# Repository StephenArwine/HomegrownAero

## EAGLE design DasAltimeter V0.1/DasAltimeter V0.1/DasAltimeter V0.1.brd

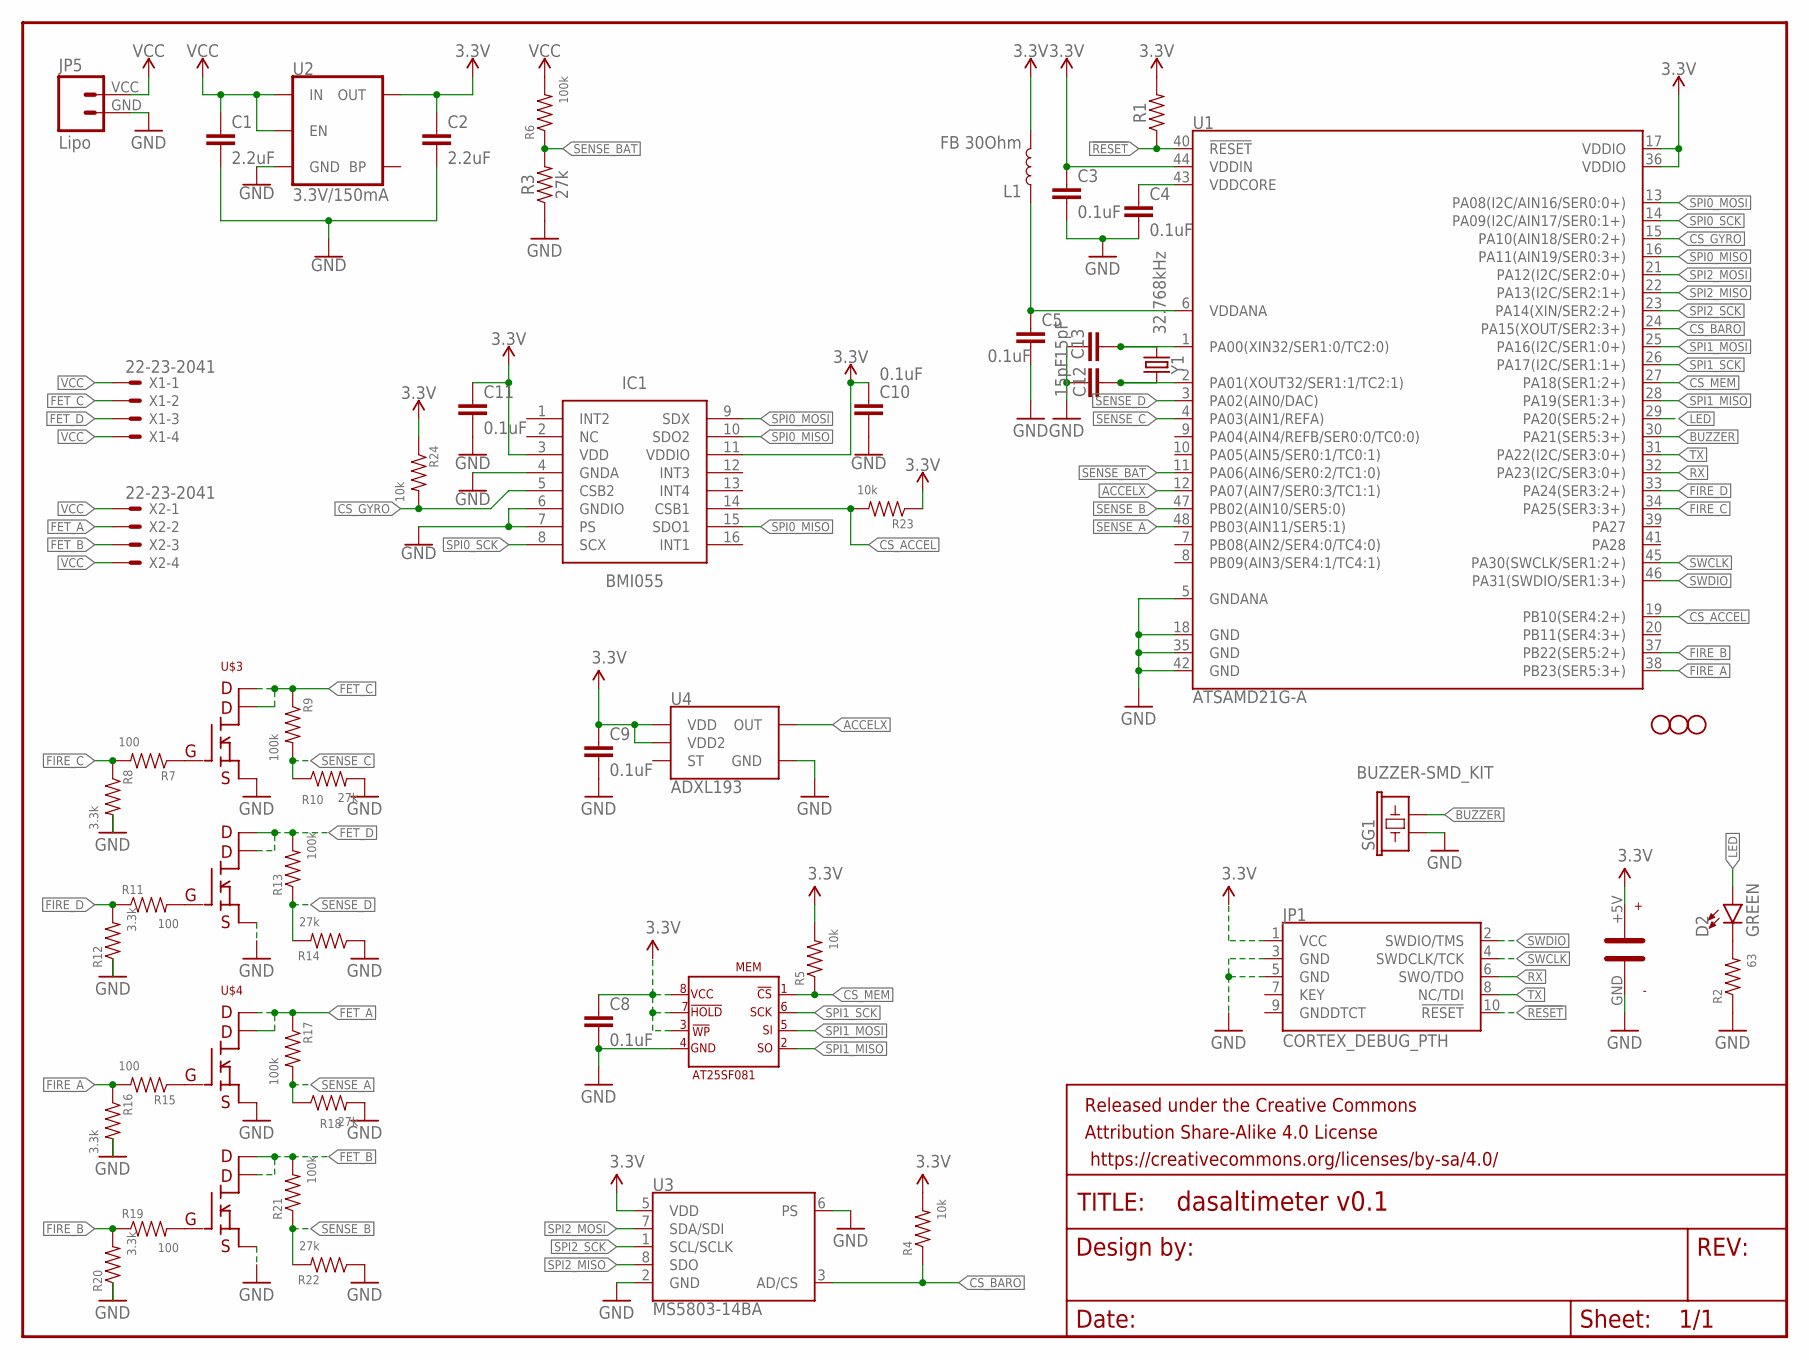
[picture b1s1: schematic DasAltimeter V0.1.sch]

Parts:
C1, C2: 2.2uF; 0603
C3, C4, C5, C8, C9, C10, C11: 0.1uF; 0402
C12, C13: 15pF; 0402
D2: GREEN; LED-1206
FRAME1: FRAME-LETTERNO_PACKAGE; DUMMY
H1, H2, H3: STAND-OFFTIGHT; STAND-OFF-TIGHT
IC1: BMI055
JP1: CORTEX_DEBUG_PTH; 2X5-PTH-1.27MM
JP5: Lipo; JST-2-SMD-VERT
L1: FB 30Ohm; 0603
MEM: AT25SF081
R1: 0402
R2: 63; 0402
R3, R10, R14, R18, R22: 27k; 0402
R4, R5, R23, R24: 10k; 0402
R6, R9, R13, R17, R21: 100k; 0402
R7, R11, R15, R19: 100; 0402
R8, R12, R16, R20: 3.3k; 0402
SG1: BUZZER-SMD_KIT; BUZZER-CCV-KIT
U1: ATSAMD21G-A; TQFP-48
U2: 3.3V/150mA; SOT23-5
U3: MS5803-14BA; MS5803
U4: ADXL193; LCC-8
U$1: PB-5R0H104-R
U$3, U$4: SI7232DN
X1, X2: 22-23-2041
Y1: 32.768kHz; CRYSTAL-SMD-3.2X1.5MM

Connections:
3.3V: C2.1, C3.1, C8.1, C9.1, C10.1, C11.1, IC1.3 (VDD), IC1.11 (VDDIO), JP1.1 (VCC), L1.2, MEM.!HOLD, MEM.!WP, MEM.VCC, R1.2, R4.2, R5.2, R23.1, R24.1, U1.17 (VDDIO), U1.36 (VDDIO), U1.44 (VDDIN), U2.5 (OUT), U3.5 (VDD), U4.P$7 (VDD), U4.P$8 (VDD2), U$1.+5V
!RESET: JP1.10 (!RESET), R1.1, U1.40 (!RESET!)
ACCELX: U1.12 (PA07(AIN7/SER0:3/TC1:1)), U4.P$6 (OUT)
BUZZER: SG1.- (2), U1.30 (PA21(SER5:3+))
CS_ACCEL: IC1.14 (CSB1), R23.2, U1.19 (PB10(SER4:2+))
CS_GYRO: IC1.5 (CSB2), R24.2, U1.15 (PA10(AIN18/SER0:2+))
CS_MEM: MEM.!CS, R5.1, U1.27 (PA18(SER1:2+))
FET_A: R17.1, U$4.7 (PIN7), U$4.8 (PIN8), U$4.9 (PIN8), X2.2
FET_B: R21.2, U$4.5 (PIN5), U$4.6 (PIN6), U$4.10 (PIN5), X2.3
FET_C: R9.1, U$3.7 (PIN7), U$3.8 (PIN8), U$3.9 (PIN8), X1.2
FET_D: R13.2, U$3.5 (PIN5), U$3.6 (PIN6), U$3.10 (PIN5), X1.3
FIRE_A: R15.2, R16.1, U1.38 (PB23(SER5:3+))
FIRE_B: R19.1, R20.2, U1.37 (PB22(SER5:2+))
FIRE_C: R7.2, R8.1, U1.34 (PA25(SER3:3+))
FIRE_D: R11.1, R12.2, U1.33 (PA24(SER3:2+))
GND: C1.2, C2.2, C3.2, C4.2, C5.2, C8.2, C9.2, C10.2, C11.2, C12.1, C13.1, IC1.4 (GNDA), IC1.6 (GNDIO), IC1.7 (PS), JP1.3 (GND), JP1.5 (GND), JP5.GND (1), MEM.GND, R2.1, R3.1, R8.2, R10.2, R12.1, R14.1, R16.2, R18.2, R20.1, R22.1, SG1.+ (1), U1.5 (GNDANA), U1.18 (GND), U1.35 (GND), U1.42 (GND), U2.2 (GND), U3.2 (GND), U3.6 (PS), U4.P$3 (GND), U$1.GND, U$3.1 (PIN1), U$3.3 (PIN3), U$4.1 (PIN1), U$4.3 (PIN3)
LED: D2.A, U1.29 (PA20(SER5:2+))
unnamed: R7.1, U$3.2 (PIN2)
unnamed: C4.1, U1.43 (VDDCORE)
unnamed: C5.1, L1.1, U1.6 (VDDANA)
unnamed: C13.2, U1.1 (PA00(XIN32/SER1:0/TC2:0)), Y1.P$2 (2)
unnamed: C12.2, U1.2 (PA01(XOUT32/SER1:1/TC2:1)), Y1.P$1 (1)
unnamed: R11.2, U$3.4 (PIN4)
unnamed: R15.1, U$4.2 (PIN2)
unnamed: R19.2, U$4.4 (PIN4)
unnamed: D2.C, R2.2
RX: JP1.6 (SWO/TDO), U1.32 (PA23(I2C/SER3:0+))
SENSE_A: R17.2, R18.1, U1.48 (PB03(AIN11/SER5:1))
SENSE_B: R21.1, R22.2, U1.47 (PB02(AIN10/SER5:0))
SENSE_BAT: R3.2, R6.1, U1.11 (PA06(AIN6/SER0:2/TC1:0))
SENSE_C: R9.2, R10.1, U1.4 (PA03(AIN1/REFA))
SENSE_D: R13.1, R14.2, U1.3 (PA02(AIN0/DAC))
SPI0_MISO: IC1.10 (SDO2), IC1.15 (SDO1), U1.16 (PA11(AIN19/SER0:3+))
SPI0_MOSI: IC1.9 (SDX), U1.13 (PA08(I2C/AIN16/SER0:0+))
SPI0_SCK: IC1.8 (SCX), U1.14 (PA09(I2C/AIN17/SER0:1+))
SPI1_MISO: MEM.SO, U1.28 (PA19(SER1:3+))
SPI1_MOSI: MEM.SI, U1.25 (PA16(I2C/SER1:0+))
SPI1_SCK: MEM.SCK, U1.26 (PA17(I2C/SER1:1+))
SPI2_MISO: U1.22 (PA13(I2C/SER2:1+)), U3.8 (SDO)
SPI2_MOSI: U1.21 (PA12(I2C/SER2:0+)), U3.7 (SDA/SDI)
SWCLK: JP1.4 (SWDCLK/TCK), U1.45 (PA30(SWCLK/SER1:2+))
SWDIO: JP1.2 (SWDIO/TMS), U1.46 (PA31(SWDIO/SER1:3+))
TX: JP1.8 (NC/TDI), U1.31 (PA22(I2C/SER3:0+))
VCC: C1.1, JP5.VCC (2), R6.2, U2.1 (IN), U2.3 (EN), X1.1, X1.4, X2.1, X2.4

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
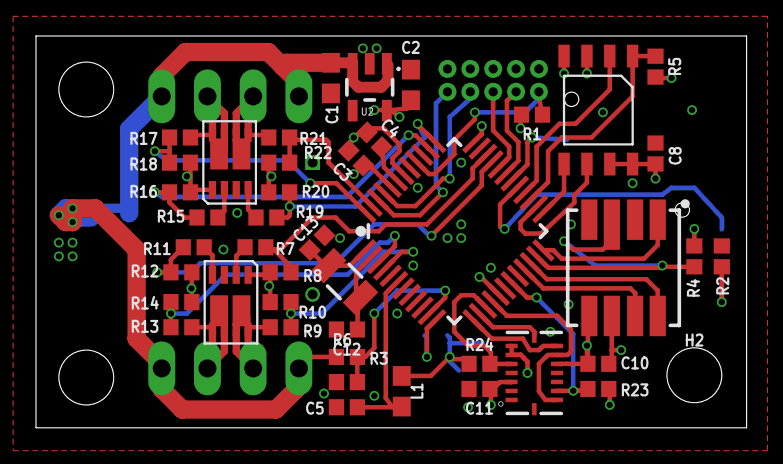
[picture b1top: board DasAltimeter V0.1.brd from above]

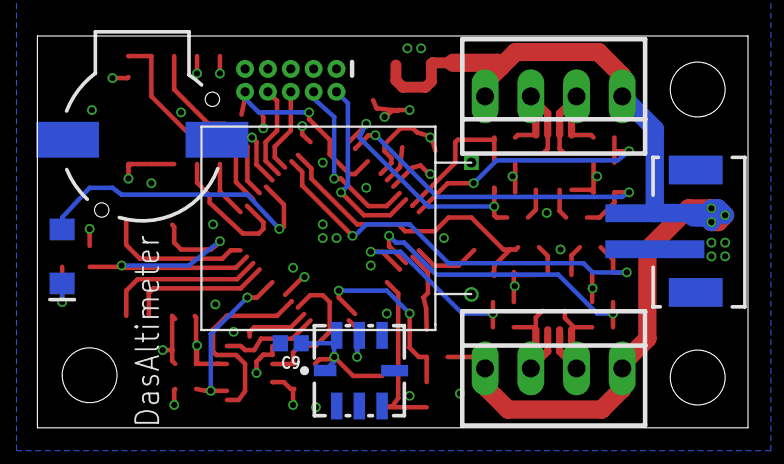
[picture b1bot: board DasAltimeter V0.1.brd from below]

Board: 4 copper layers, 39.5 x 21.8 mm, 56 parts (9 on the bottom side), 46 nets.

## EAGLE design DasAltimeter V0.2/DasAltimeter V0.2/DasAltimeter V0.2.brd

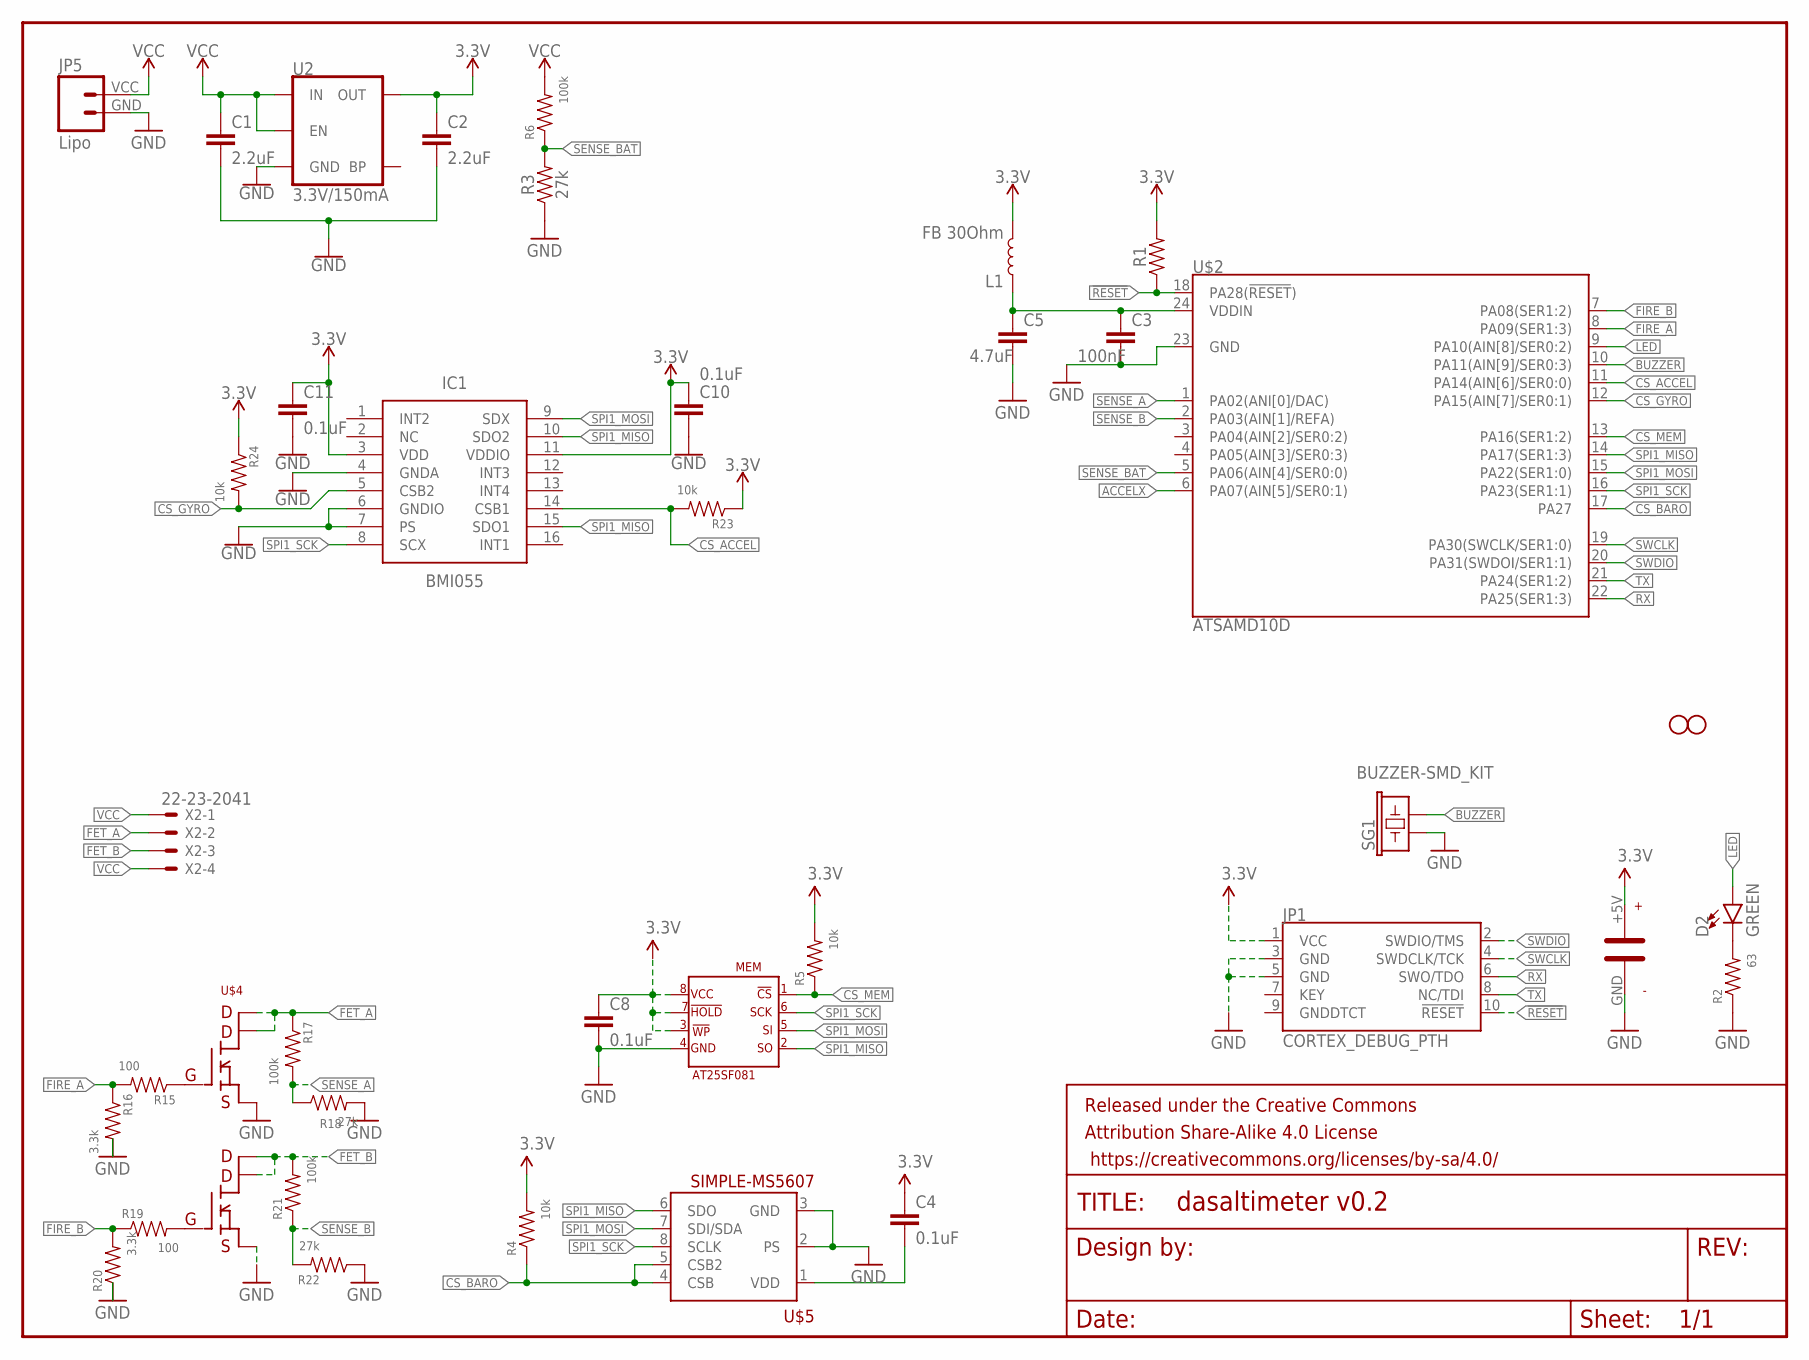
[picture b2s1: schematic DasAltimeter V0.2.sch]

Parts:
C1, C2: 2.2uF; 0603
C3: 100nF; 0402
C4, C8, C10, C11: 0.1uF; 0402
C5: 4.7uF; 0402
D2: GREEN; LED-1206
FRAME1: FRAME-LETTERNO_PACKAGE; DUMMY
H2, H3: STAND-OFFTIGHT; STAND-OFF-TIGHT
IC1: BMI055
JP1: CORTEX_DEBUG_PTH; 2X5-PTH-1.27MM
JP5: Lipo; JST-2-SMD-VERT
L1: FB 30Ohm; 0603
MEM: AT25SF081
R1: 0402
R2: 63; 0402
R3, R18, R22: 27k; 0402
R4, R5, R23, R24: 10k; 0402
R6, R17, R21: 100k; 0402
R15, R19: 100; 0402
R16, R20: 3.3k; 0402
SG1: BUZZER-SMD_KIT; BUZZER-CCV-KIT
U2: 3.3V/150mA; SOT23-5
U$1: PB-5R0H104-R
U$2: ATSAMD10D
U$4: SI7232DN
U$5: SIMPLE-MS5607; MS5607
X2: 22-23-2041

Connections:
3.3V: C2.1, C4.1, C8.1, C10.1, C11.1, IC1.3 (VDD), IC1.11 (VDDIO), JP1.1 (VCC), L1.2, MEM.!HOLD, MEM.!WP, MEM.VCC, R1.2, R4.2, R5.2, R23.1, R24.1, U2.5 (OUT), U$1.+5V
!RESET: JP1.10 (!RESET), R1.1, U$2.18 (PA28(!RESET!))
ACCELX: U$2.6 (PA07(AIN[5]/SER0:1))
BUZZER: SG1.- (2), U$2.10 (PA11(AIN[9]/SER0:3))
CS_ACCEL: IC1.14 (CSB1), R23.2, U$2.11 (PA14(AIN[6]/SER0:0))
CS_BARO: R4.1, U$2.17 (PA27), U$5.5 (CSB2)
CS_GYRO: IC1.5 (CSB2), R24.2, U$2.12 (PA15(AIN[7]/SER0:1))
CS_MEM: MEM.!CS, R5.1, U$2.13 (PA16(SER1:2))
FET_A: R17.1, U$4.7 (PIN7), U$4.8 (PIN8), U$4.9 (PIN8), X2.2
FET_B: R21.2, U$4.5 (PIN5), U$4.6 (PIN6), U$4.10 (PIN5), X2.3
FIRE_A: R15.2, R16.1, U$2.8 (PA09(SER1:3))
FIRE_B: R19.1, R20.2, U$2.7 (PA08(SER1:2))
GND: C1.2, C2.2, C3.2, C5.2, C8.2, C10.2, C11.2, IC1.4 (GNDA), IC1.6 (GNDIO), IC1.7 (PS), JP1.3 (GND), JP1.5 (GND), JP5.GND (1), MEM.GND, R2.1, R3.1, R16.2, R18.2, R20.1, R22.1, SG1.+ (1), U2.2 (GND), U$1.GND, U$2.23 (GND), U$4.1 (PIN1), U$4.3 (PIN3), U$5.3 (GND)
LED: D2.A, U$2.9 (PA10(AIN[8]/SER0:2))
unnamed: C4.2, U$5.1 (VDD)
unnamed: C3.1, C5.1, L1.1, U$2.24 (VDDIN)
unnamed: R15.1, U$4.2 (PIN2)
unnamed: R19.2, U$4.4 (PIN4)
unnamed: D2.C, R2.2
RX: JP1.6 (SWO/TDO), U$2.22 (PA25(SER1:3))
SENSE_A: R17.2, R18.1, U$2.1 (PA02(ANI[0]/DAC))
SENSE_B: R21.1, R22.2, U$2.2 (PA03(AIN[1]/REFA))
SENSE_BAT: R3.2, R6.1, U$2.5 (PA06(AIN[4]/SER0:0))
SPI1_MISO: IC1.10 (SDO2), IC1.15 (SDO1), MEM.SO, U$2.14 (PA17(SER1:3))
SPI1_MOSI: IC1.9 (SDX), MEM.SI, U$2.15 (PA22(SER1:0))
SPI1_SCK: IC1.8 (SCX), MEM.SCK, U$2.16 (PA23(SER1:1))
SWCLK: JP1.4 (SWDCLK/TCK), U$2.19 (PA30(SWCLK/SER1:0))
SWDIO: JP1.2 (SWDIO/TMS), U$2.20 (PA31(SWDOI/SER1:1))
TX: JP1.8 (NC/TDI), U$2.21 (PA24(SER1:2))
VCC: C1.1, JP5.VCC (2), R6.2, U2.1 (IN), U2.3 (EN), X2.1, X2.4

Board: 4 copper layers, 40 parts (9 on the bottom side), 29 nets, no tracks yet.

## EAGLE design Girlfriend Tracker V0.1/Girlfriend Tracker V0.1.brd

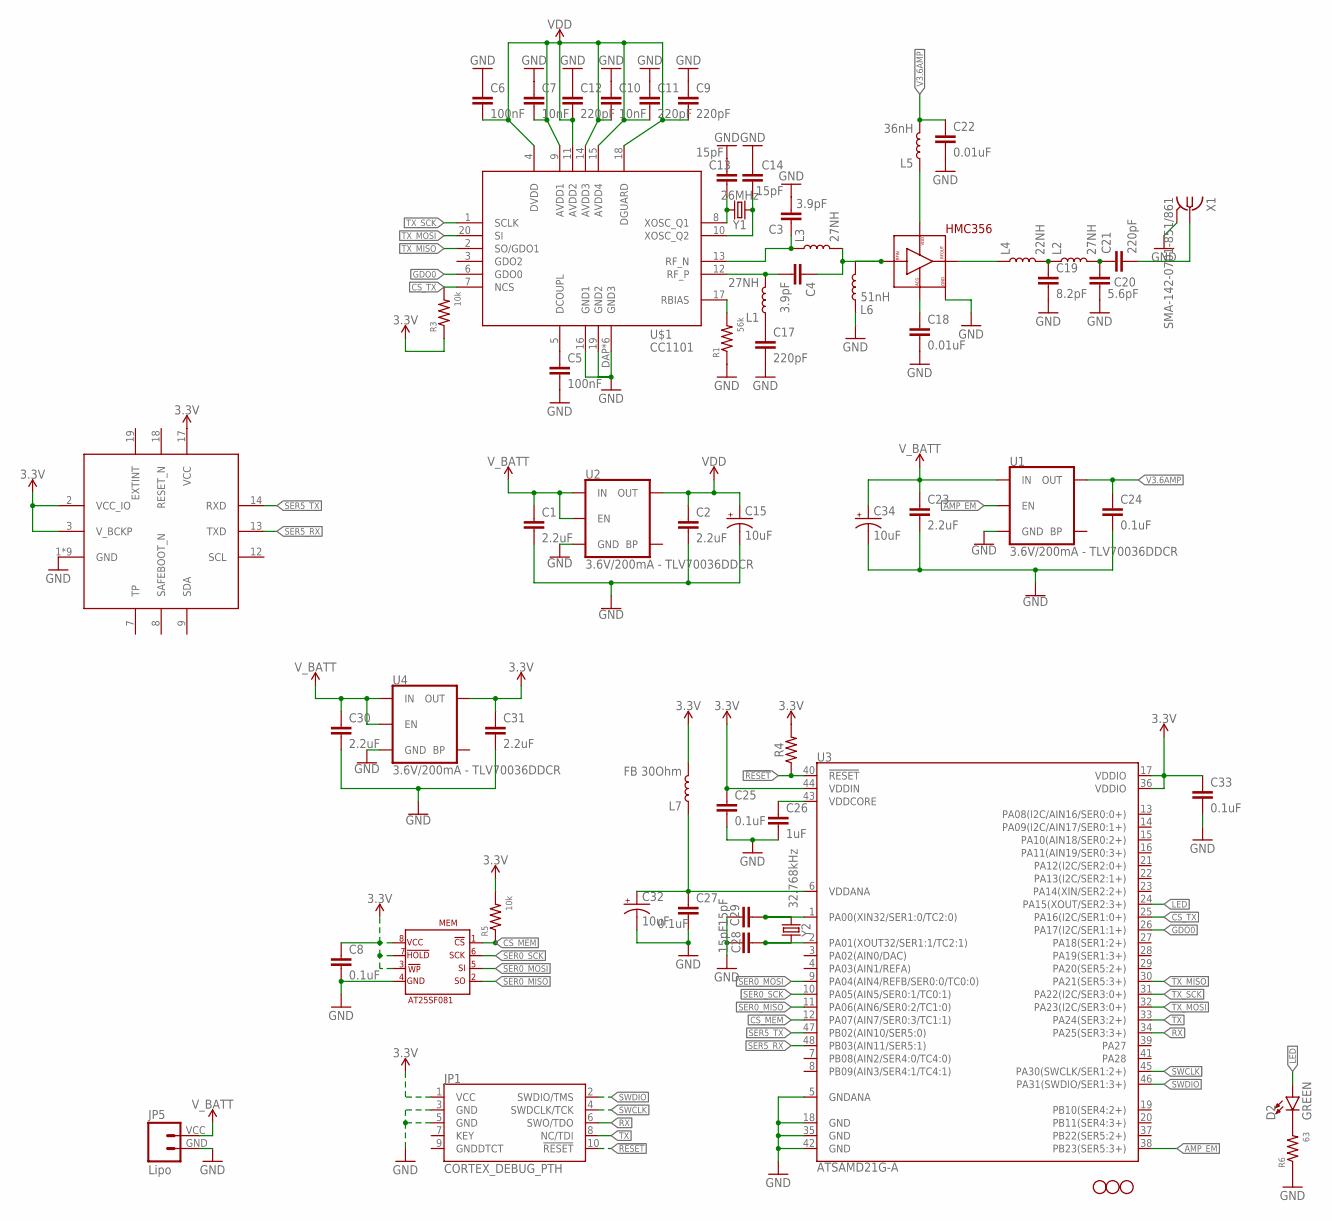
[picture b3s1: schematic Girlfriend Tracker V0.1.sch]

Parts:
C1, C2, C23, C30, C31: 2.2uF; 0603
C3, C4: 3.9pF; 0402
C5, C6: 100nF; 0402
C7, C10: 10nF; 0402
C8, C25, C27, C33: 0.1uF; 0402
C9, C11, C12, C17, C21: 220pF; 0402
C13, C14, C28, C29: 15pF; 0402
C15, C32, C34: 10uF; EIA3216
C18, C22: 0.01uF; 0402
C19: 8.2pF; 0402
C20: 5.6pF; 0402
C24: 0.1uF; 0603
C26: 1uF; 0402
D2: GREEN; LED-1206
H1, H2, H3: STAND-OFFTIGHT; STAND-OFF-TIGHT
IC1: SAM-M8Q
JP1: CORTEX_DEBUG_PTH; 2X5-PTH-1.27MM
JP5: Lipo; JST-2-SMD-VERT
L1, L2, L3: 27NH; 0402
L4: 22NH; 0402
L5: 36nH; 0402
L6: 51nH; 0402
L7: FB 30Ohm; 0603
MEM: AT25SF081
R1: 56k; 0402
R3, R5: 10k; 0402
R4: 0402
R6: 63; 0402
U1, U2, U4: 3.6V/200mA - TLV70036DDCR; SOT23-5
U3: ATSAMD21G-A; TQFP-48
U$1: CC1101
U$3: HMC356; QFN16_HMC356
X1: SMA-142-0701-851/861; J502-ND-142-0701-851/861
Y1: 26MHz; CRYSTAL-SMD-3.2X2.5MM
Y2: 32.768kHz; CRYSTAL-SMD-3.2X1.5MM

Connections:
3.3V: C8.1, C25.1, C31.1, C33.1, IC1.2 (VCC_IO), IC1.3 (V_BCKP), IC1.17 (VCC), JP1.1 (VCC), L7.2, MEM.!HOLD, MEM.!WP, MEM.VCC, R3.1, R4.2, R5.2, U3.17 (VDDIO), U3.36 (VDDIO), U3.44 (VDDIN), U4.5 (OUT)
!RESET: JP1.10 (!RESET), R4.1, U3.40 (!RESET!)
AMP_EM: U1.3 (EN), U3.38 (PB23(SER5:3+))
CS_MEM: MEM.!CS, R5.1, U3.12 (PA07(AIN7/SER0:3/TC1:1))
CS_TX: R3.2, U3.25 (PA16(I2C/SER1:0+)), U$1.7 (NCS)
GDO0: U3.26 (PA17(I2C/SER1:1+)), U$1.6 (GDO0)
GND: C1.2, C2.2, C3.2, C5.2, C6.1, C7.1, C8.2, C9.1, C10.1, C11.1, C12.1, C13.1, C14.2, C15.C (-), C17.2, C18.2, C19.2, C20.2, C22.2, C23.2, C24.2, C25.2, C26.2, C27.2, C28.1, C29.1, C30.2, C31.2, C32.C (-), C33.2, C34.C (-), IC1.1 (GND), IC1.4 (GND), IC1.5 (GND), IC1.6 (GND), IC1.10 (GND), IC1.11 (GND), IC1.15 (GND), IC1.16 (GND), IC1.20 (GND), JP1.3 (GND), JP1.5 (GND), JP5.GND (1), L6.1, MEM.GND, R1.1, R6.1, U1.2 (GND), U2.2 (GND), U3.5 (GNDANA), U3.18 (GND), U3.35 (GND), U3.42 (GND), U4.2 (GND), U$1.16 (GND1), U$1.19 (GND2), U$1.DAP (GND3), U$1.P$1 (GND3), U$1.P$2 (GND3), U$1.P$3 (GND3), U$1.P$4 (GND3), U$1.P$5 (GND3), U$3.P$2, U$3.P$4, U$3.P$6, U$3.P$16, U$3.P$17, U$3.P$17_1, U$3.P$17_2, U$3.P$17_3, U$3.P$17_4, X1.G@1 (2), X1.G@2 (2), X1.G@3 (2), X1.G@4 (2)
LED: D2.A, U3.24 (PA15(XOUT/SER2:3+))
unnamed: C17.1, L1.1
unnamed: C19.1, L2.1, L4.2
unnamed: C13.2, U$1.8 (XOSC_Q1), Y1.3 (2)
unnamed: C20.1, C21.1, L2.2
unnamed: C5.1, U$1.5 (DCOUPL)
unnamed: R1.2, U$1.17 (RBIAS)
unnamed: C18.1, U$3.P$7
unnamed: C21.2, X1.1
unnamed: L5.1, U$3.P$15
unnamed: C4.1, L3.2, L6.2, U$3.P$3
unnamed: C26.1, U3.43 (VDDCORE)
unnamed: C27.1, C32.A (+), L7.1, U3.6 (VDDANA)
unnamed: C29.2, U3.1 (PA00(XIN32/SER1:0/TC2:0)), Y2.P$2 (2)
unnamed: C28.2, U3.2 (PA01(XOUT32/SER1:1/TC2:1)), Y2.P$1 (1)
unnamed: L4.1, U$3.P$11
unnamed: C14.1, U$1.10 (XOSC_Q2), Y1.1
unnamed: D2.C, R6.2
RF_N: C3.1, L3.1, U$1.13 (RF_N)
RF_P: C4.2, L1.2, U$1.12 (RF_P)
RX: JP1.6 (SWO/TDO), U3.34 (PA25(SER3:3+))
SER0_MISO: MEM.SO, U3.11 (PA06(AIN6/SER0:2/TC1:0))
SER0_MOSI: MEM.SI, U3.9 (PA04(AIN4/REFB/SER0:0/TC0:0))
SER0_SCK: MEM.SCK, U3.10 (PA05(AIN5/SER0:1/TC0:1))
SER5_RX: IC1.13 (TXD), U3.48 (PB03(AIN11/SER5:1))
SER5_TX: IC1.14 (RXD), U3.47 (PB02(AIN10/SER5:0))
SWCLK: JP1.4 (SWDCLK/TCK), U3.45 (PA30(SWCLK/SER1:2+))
SWDIO: JP1.2 (SWDIO/TMS), U3.46 (PA31(SWDIO/SER1:3+))
TX: JP1.8 (NC/TDI), U3.33 (PA24(SER3:2+))
TX_MISO: U3.30 (PA21(SER5:3+)), U$1.2 (SO/GDO1)
TX_MOSI: U3.32 (PA23(I2C/SER3:0+)), U$1.20 (SI)
TX_SCK: U3.31 (PA22(I2C/SER3:0+)), U$1.1 (SCLK)
V3.6AMP: C22.1, C24.1, L5.2, U1.5 (OUT)
VDD: C2.1, C6.2, C7.2, C9.2, C10.2, C11.2, C12.2, C15.A (+), U2.5 (OUT), U$1.4 (DVDD), U$1.9 (AVDD1), U$1.11 (AVDD2), U$1.14 (AVDD3), U$1.15 (AVDD4), U$1.18 (DGUARD)
V_BATT: C1.1, C23.1, C30.1, C34.A (+), JP5.VCC (2), U1.1 (IN), U2.1 (IN), U2.3 (EN), U4.1 (IN), U4.3 (EN)

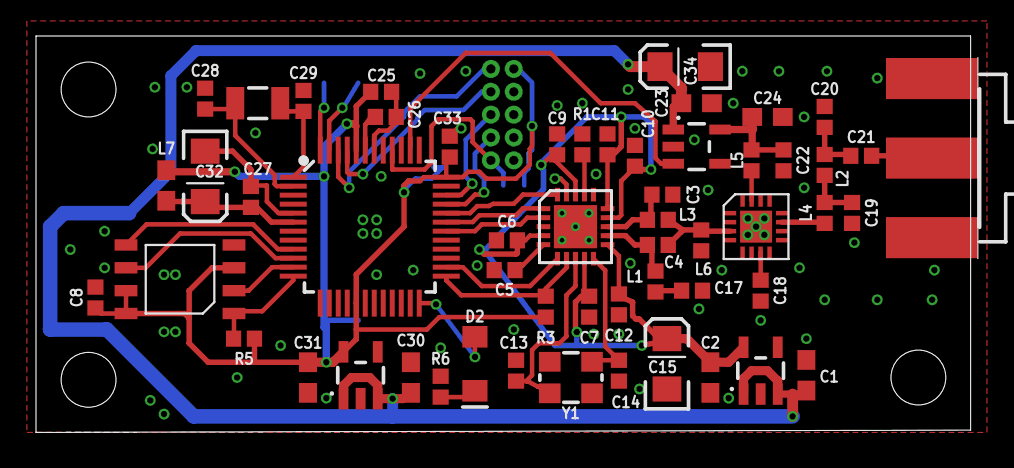
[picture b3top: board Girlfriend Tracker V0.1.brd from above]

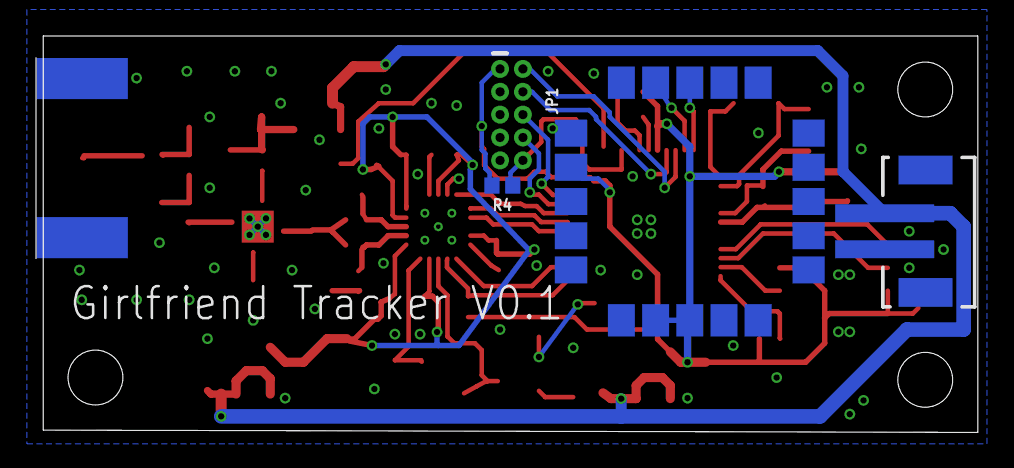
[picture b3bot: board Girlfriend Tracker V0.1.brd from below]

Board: 2 copper layers, 51.9 x 22.0 mm, 62 parts (4 on the bottom side), 42 nets.

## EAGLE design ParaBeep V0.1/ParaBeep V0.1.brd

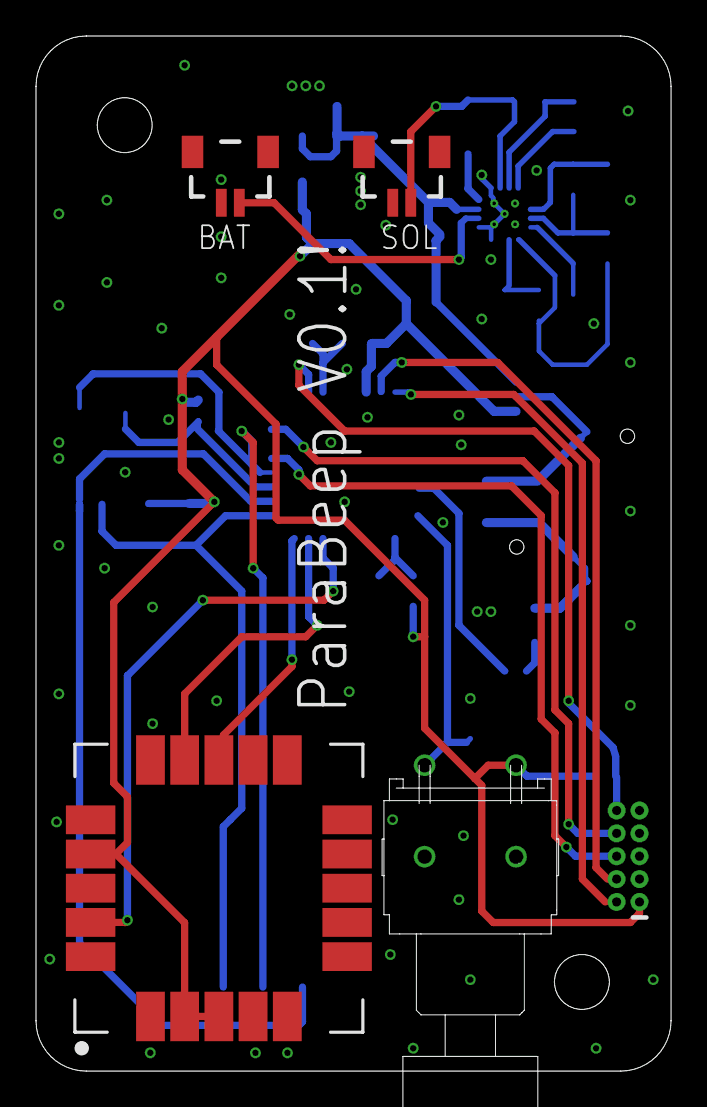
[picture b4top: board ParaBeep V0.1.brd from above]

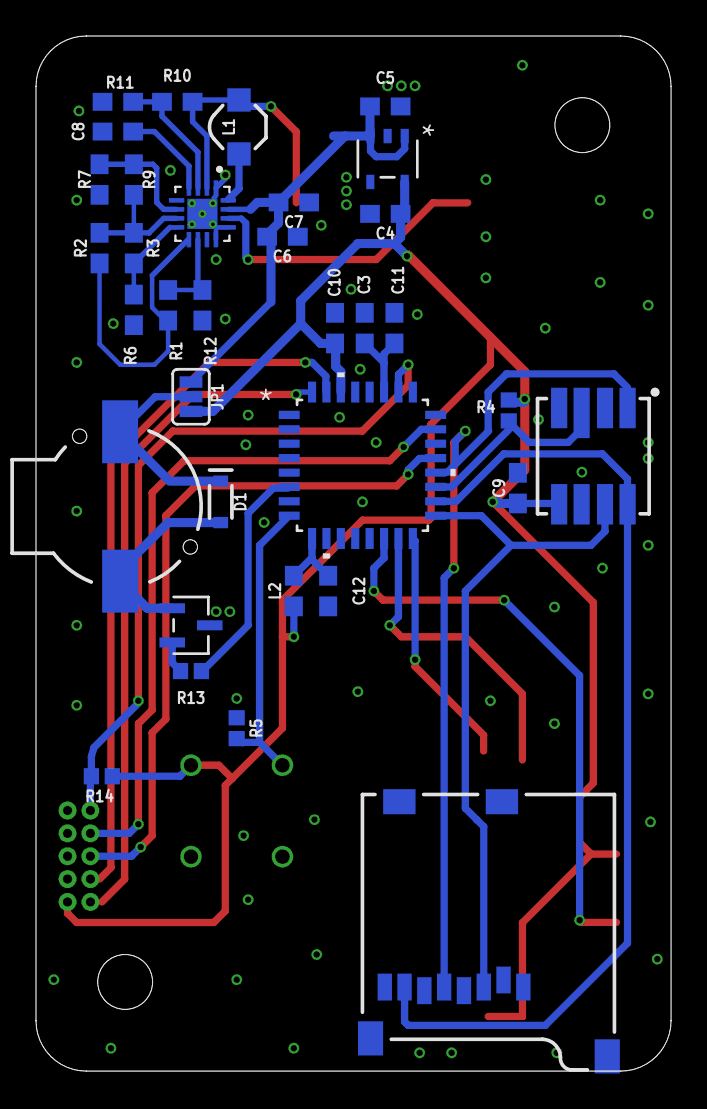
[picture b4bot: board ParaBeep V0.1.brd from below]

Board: 2 copper layers, 35.3 x 57.5 mm, 41 parts (34 on the bottom side), 32 nets.

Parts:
BAT: SM02B-SSR-H-TB
C3, C4, C5: 1.0uF; 0603
C6: 4.7uF; 0603
C7, C9, C10, C11, C12: 0.1uF; 0603
C8: 10nF; 0603
D1: 250mA/100V; SOD-323
H1, H2: STAND-OFFTIGHT; STAND-OFF-TIGHT
J1: MICRO-SD_CARD_SOCKETPUSH-PUSH; MICRO-SD-SOCKET
JP1: JUMPER-SMT_3_NO_SILK; SMT-JUMPER_3_NO_SILK
JP3: CORTEX_DEBUG_PTH; 2X5-PTH-1.27MM
L1: 4.7µH/±30%/1.2A; INDUCTOR_4.7UH
L2: 0603
R1, R3: 6.19M; 0603
R2: 542K; 0603
R4, R5, R13, R14: 0402
R6: 3.83M; 0603
R7, R10: 4.42M; 0603
R8: 2SC2412KT146R; TRANS_2SB852K_ROM
R9: 5.65M; 0603
R11: 15M; 0603
R12: 3.32M; 0603
SG1: BUZZER-SMD_KIT; BUZZER-CCV-KIT
SOL: SM02B-SSR-H-TB
U1: BQ25504RGTR; QFN50P300X300X100-17N
U3: TPS78330DDCRDDC5_TEX-L; DDC5_TEX-L
U4: UBLOX_SAM_M8Q-0-10; SAM-M8Q
U5: MS5803-14BA; MS5803
U6: ATSAML10E16A-AFTTQFP32_MC_MCH-L; TQFP32_MC_MCH-L
U$3: AB11AH-HC

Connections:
!RESET: JP3.10, R14.1, U6.26
BUTTON: R5.2, U6.8, U$3.P$1
BUZZER: R13.2, U6.6
CS_BARO: R4.1, U5.3, U6.19
GND: BAT.2, C3.2, C4.2, C5.2, C6.1, C7.1, C8.1, C9.2, C10.2, C11.2, C12.2, JP3.3, JP3.5, R5.1, R6.2, R7.2, R8.3, R11.2, R12.2, SOL.2, U1.1, U1.12, U1.13, U1.17, U3.2, U3.4, U4.1, U4.4, U4.5, U4.6, U4.10, U4.11, U4.15, U4.16, U4.20, U5.2, U5.6, U6.10, U6.28
GPS_INT: U4.19, U6.14
unnamed: C3.1, C11.1, U6.27
unnamed: D1.C, JP1.2, SG1.-
unnamed: R2.2, R3.1, R9.1, U1.7
unnamed: R3.2, R6.1, U1.8
unnamed: R7.1, R9.2, U1.6
unnamed: R1.2, R2.1, U1.9
unnamed: R1.1, R12.1, U1.10
unnamed: C8.2, U1.4
unnamed: D1.A, R8.1, SG1.+
unnamed: R10.2, R11.1, U1.3
unnamed: L1.P$1, R10.1, SOL.1, U1.2
unnamed: R8.2, R13.1
unnamed: L1.P$2, U1.16
unnamed: BAT.1, U1.14
unnamed: C12.1, L2.2, U6.9
RX: JP3.6, U6.21
SPI_MISO: J1.DO, U5.8, U6.18
SPI_MOSI: J1.DI, U5.7, U6.17
SPI_SCK: J1.SCLK, U5.1, U6.20
SWCLK: JP3.4, U6.31
SWDIO: JP3.2, U6.32
TX: JP3.8, U6.23
USART_RX: U4.13, U6.16
USART_TX: U4.14, U6.15
VCC_1: C4.1, C9.1, C10.1, JP1.3, JP3.1, L2.1, R4.2, R14.2, U3.5, U4.2, U4.3, U4.17, U5.5, U6.30, U$3.P$2
VIN: C5.1, C6.2, C7.2, JP1.1, U1.15, U3.1, U3.3

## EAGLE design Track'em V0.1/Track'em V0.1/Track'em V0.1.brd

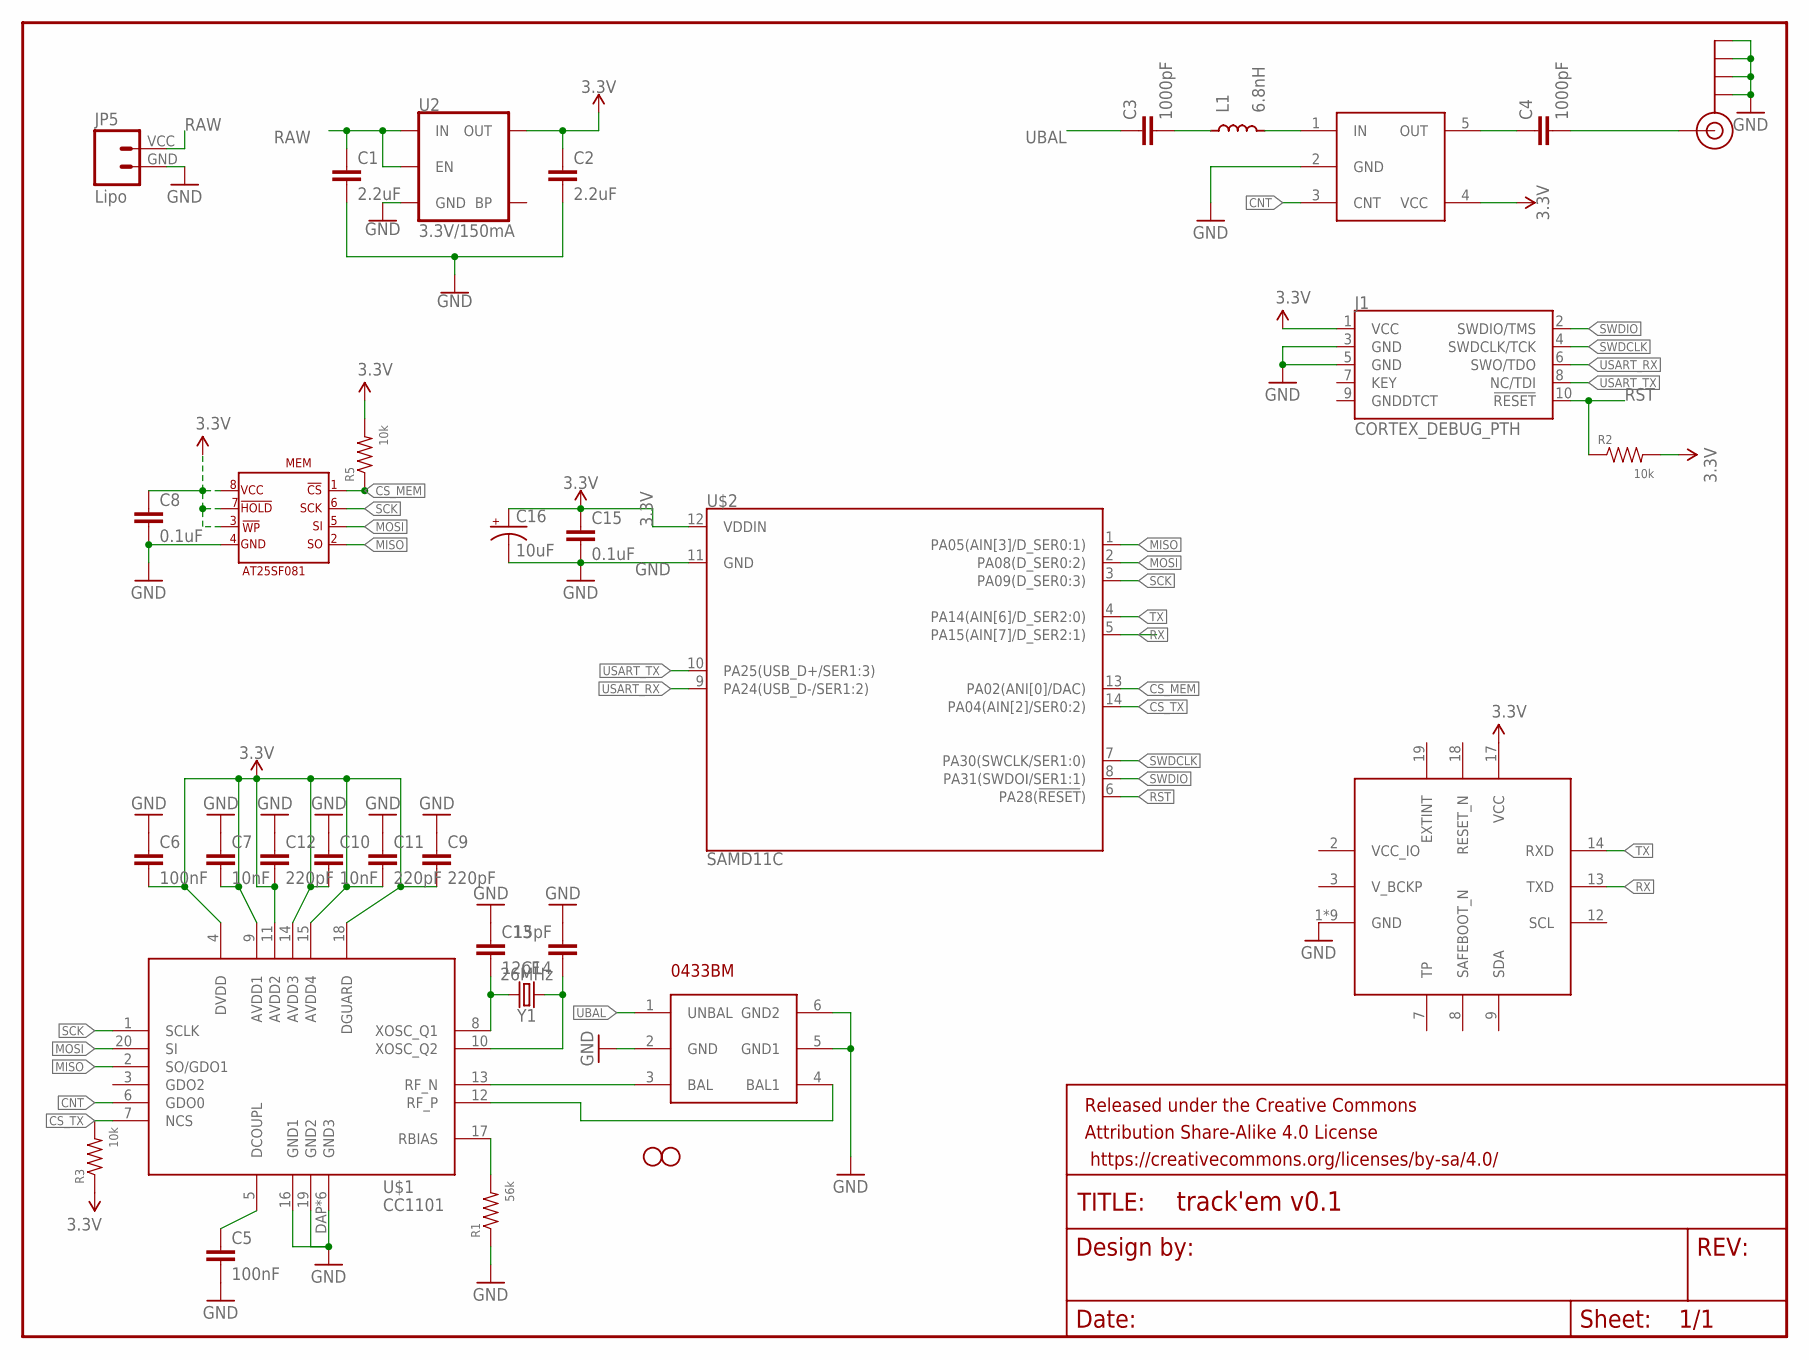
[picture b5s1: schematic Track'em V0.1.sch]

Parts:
C1, C2: 2.2uF; 0603
C3, C4: 1000pF; 0603
C5, C6: 100nF; 0402
C7, C10: 10nF; 0402
C8, C15: 0.1uF; 0402
C9, C11, C12: 220pF; 0402
C13: 12pF; 0402
C14: 15pF; 0402
C16: 10uF; 0603-POL
FRAME1: FRAME-LETTERNO_PACKAGE; DUMMY
H1, H2: STAND-OFFTIGHT; STAND-OFF-TIGHT
IC1: SAM-M8Q
J1: CORTEX_DEBUG_PTH; 2X5-PTH-1.27MM
J$1: SMA_EDGE; SMA-EDGE
JP5: Lipo; JST-2-SMD-VERT
L1: 6.8nH; 0603
MEM: AT25SF081
R1: 56k; 0402
R2, R3, R5: 10k; 0402
U2: 3.3V/150mA; SOT23-5
U$1: CC1101
U$2: SAMD11C
U$3: 0433BM15A0001
U$4: AN26018A
Y1: 26MHz; CRYSTAL-SMD-3.2X2.5MM

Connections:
3.3V: C2.1, C6.2, C7.2, C8.1, C9.2, C10.2, C11.2, C12.2, C15.1, C16.A (+), IC1.17 (VCC), J1.1 (VCC), MEM.!HOLD, MEM.!WP, MEM.VCC, R2.2, R3.1, R5.2, U2.5 (OUT), U$1.4 (DVDD), U$1.9 (AVDD1), U$1.11 (AVDD2), U$1.14 (AVDD3), U$1.15 (AVDD4), U$1.18 (DGUARD), U$2.12 (VDDIN), U$4.4 (VCC)
CNT: U$1.6 (GDO0), U$4.3 (CNT)
CS_MEM: MEM.!CS, R5.1, U$2.13 (PA02(ANI[0]/DAC))
CS_TX: R3.2, U$1.7 (NCS), U$2.14 (PA04(AIN[2]/SER0:2))
GND: C1.2, C2.2, C5.2, C6.1, C7.1, C8.2, C9.1, C10.1, C11.1, C12.1, C13.1, C14.2, C15.2, C16.K (-), IC1.1 (GND), IC1.4 (GND), IC1.5 (GND), IC1.6 (GND), IC1.10 (GND), IC1.11 (GND), IC1.15 (GND), IC1.16 (GND), IC1.20 (GND), J1.3 (GND), J1.5 (GND), J$1.GND@0 (GND), J$1.GND@1 (GND), J$1.GND@2 (GND), J$1.GND@3 (GND), JP5.GND (1), MEM.GND, R1.1, U2.2 (GND), U$1.16 (GND1), U$1.19 (GND2), U$1.DAP (GND3), U$1.P$1 (GND3), U$1.P$2 (GND3), U$1.P$3 (GND3), U$1.P$4 (GND3), U$1.P$5 (GND3), U$2.11 (GND), U$3.2 (GND), U$3.5 (GND1), U$3.6 (GND2), U$4.2 (GND)
MISO: MEM.SO, U$1.2 (SO/GDO1), U$2.1 (PA05(AIN[3]/D_SER0:1))
MOSI: MEM.SI, U$1.20 (SI), U$2.2 (PA08(D_SER0:2))
unnamed: L1.2, U$4.1 (IN)
unnamed: C3.2, L1.1
unnamed: C4.1, U$4.5 (OUT)
unnamed: C13.2, U$1.8 (XOSC_Q1), Y1.3 (2)
unnamed: C5.1, U$1.5 (DCOUPL)
unnamed: R1.2, U$1.17 (RBIAS)
unnamed: C4.2, J$1.SIG (SIGNAL)
unnamed: C14.1, U$1.10 (XOSC_Q2), Y1.1
RAW: C1.1, JP5.VCC (2), U2.1 (IN), U2.3 (EN)
RF_N: U$1.13 (RF_N), U$3.3 (BAL)
RF_P: U$1.12 (RF_P), U$3.4 (BAL1)
RST: J1.10 (!RESET), R2.1, U$2.6 (PA28(!RESET!))
RX: IC1.13 (TXD), U$2.5 (PA15(AIN[7]/D_SER2:1))
SCK: MEM.SCK, U$1.1 (SCLK), U$2.3 (PA09(D_SER0:3))
SWDCLK: J1.4 (SWDCLK/TCK), U$2.7 (PA30(SWCLK/SER1:0))
SWDIO: J1.2 (SWDIO/TMS), U$2.8 (PA31(SWDOI/SER1:1))
TX: IC1.14 (RXD), U$2.4 (PA14(AIN[6]/D_SER2:0))
UBAL: C3.1, U$3.1 (UNBAL)
USART_RX: J1.6 (SWO/TDO), U$2.9 (PA24(USB_D-/SER1:2))
USART_TX: J1.8 (NC/TDI), U$2.10 (PA25(USB_D+/SER1:3))

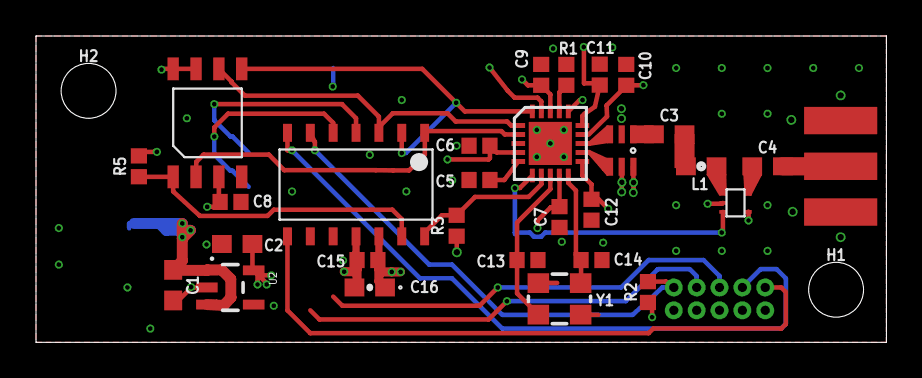
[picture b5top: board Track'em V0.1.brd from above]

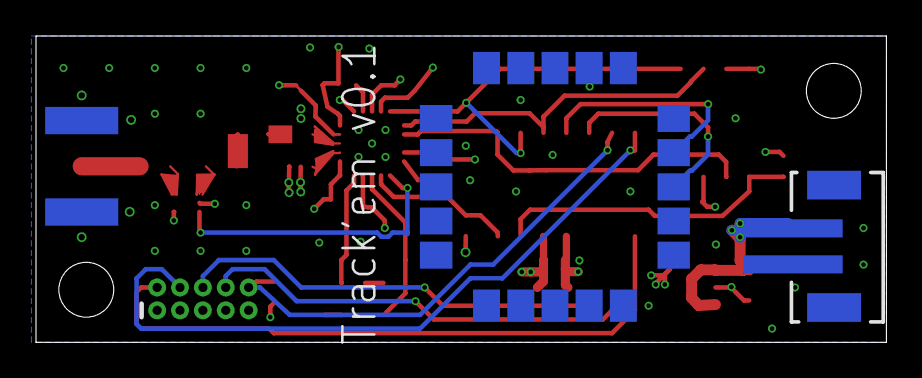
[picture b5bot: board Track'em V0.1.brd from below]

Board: 4 copper layers, 47.2 x 17.0 mm, 35 parts (3 on the bottom side), 27 nets.

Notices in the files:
parts and their libraries:
SparkFun-Capacitors: Licensing: Creative Commons ShareAlike 4.0 International - https://creativecommons.org/licenses/by-sa/4.0
SparkFun-Aesthetics: Released under the Creative Commons Attribution Share-Alike 4.0 License
SparkFun-Aesthetics: https://creativecommons.org/licenses/by-sa/4.0
